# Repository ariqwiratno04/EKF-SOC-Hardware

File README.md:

# Extended kalman FIilter for SoC Estimation

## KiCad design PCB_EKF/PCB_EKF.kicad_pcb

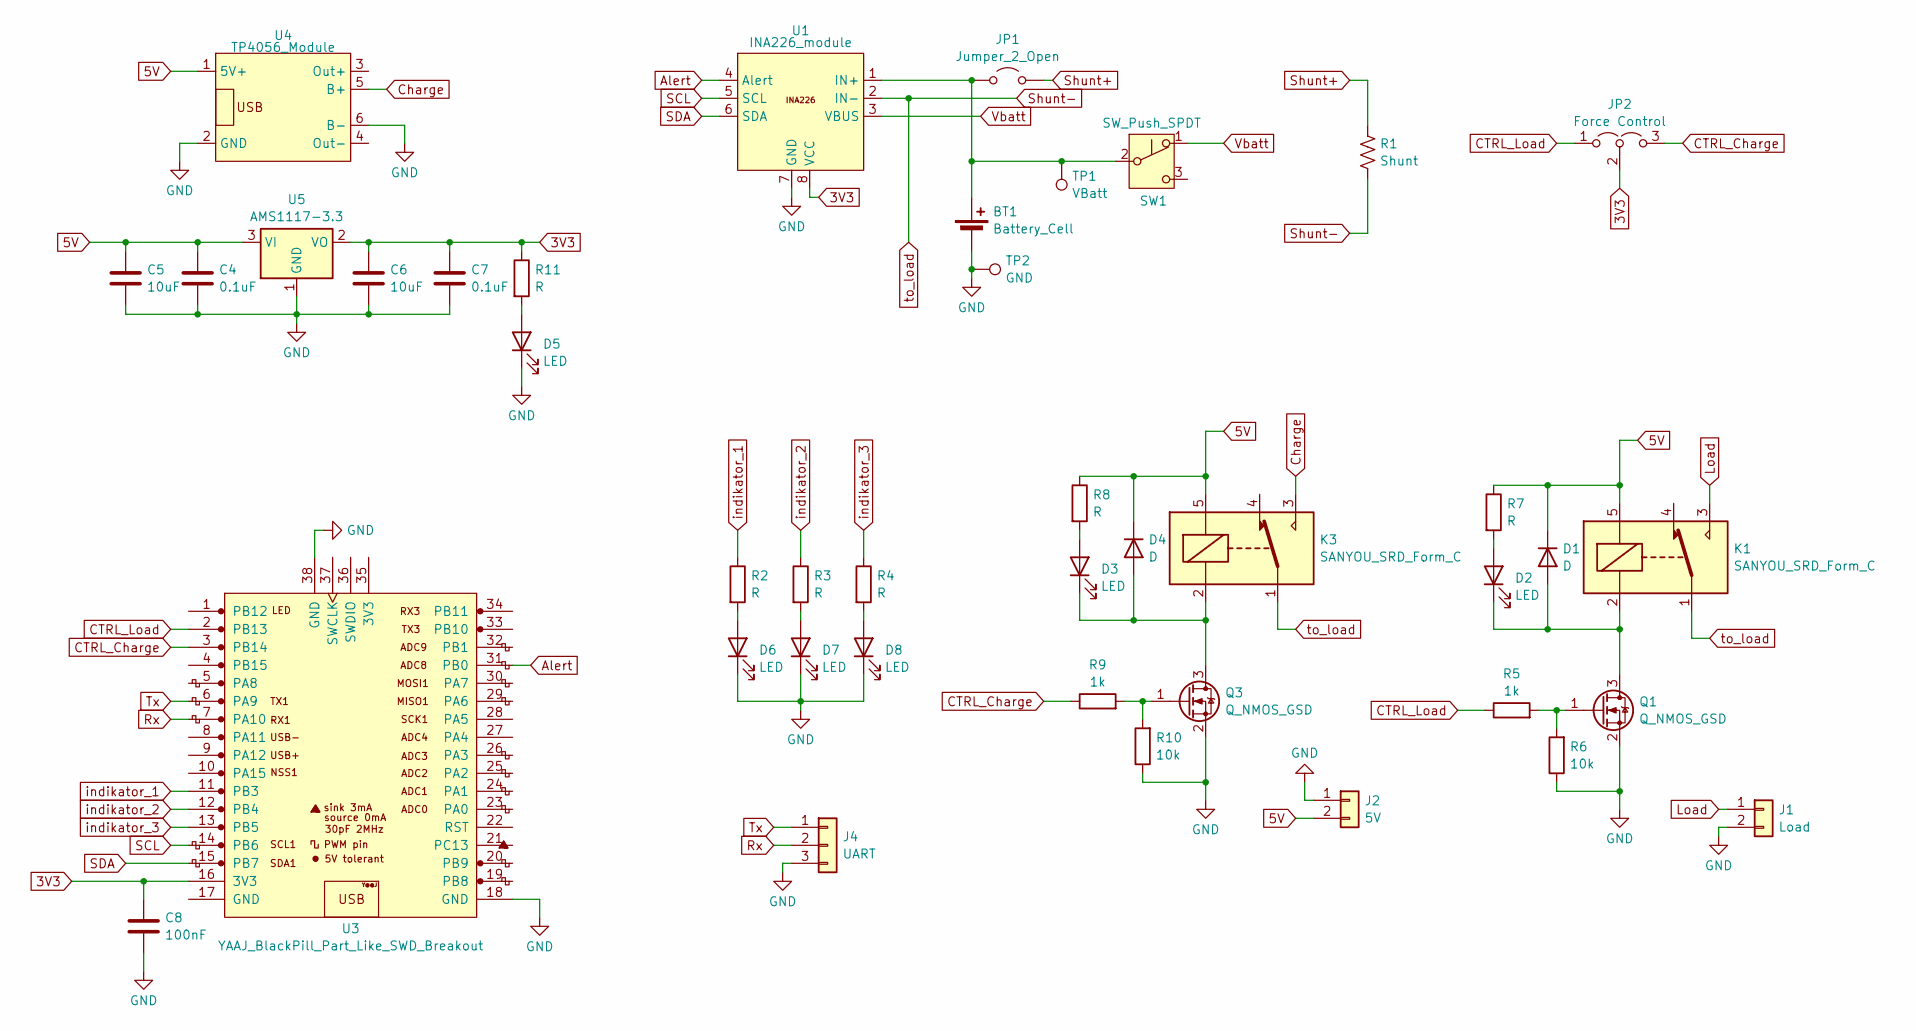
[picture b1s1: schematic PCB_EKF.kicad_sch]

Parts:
BT1: Battery_Cell; BatteryHolder_MPD_BH-18650-PC2
C4, C7: 0.1uF; C_0805_2012Metric
C5, C6: 10uF; C_0805_2012Metric
C8: 100nF; C_0805_2012Metric
D1, D4: D; D_SMA_Handsoldering
D2, D3, D5, D6, D7, D8: LED; LED_0805_2012Metric_Pad1.15x1.40mm_HandSolder
J1: Load; TerminalBlock_Phoenix_MKDS-1,5-2_1x02_P5.00mm_Horizontal
J2: 5V; TerminalBlock_Phoenix_MKDS-1,5-2_1x02_P5.00mm_Horizontal
J4: UART; PinHeader_1x03_P2.54mm_Vertical
JP1: Jumper_2_Open; SolderJumper-2_P1.3mm_Open_RoundedPad1.0x1.5mm
JP2: Force Control; PinHeader_1x03_P2.54mm_Vertical
K1, K3: SANYOU_SRD_Form_C; Relay_SPDT_SANYOU_SRD_Series_Form_C
Q1, Q3: Q_NMOS_GSD; SOT-23-3
R1: Shunt; R_2512_6332Metric_Pad1.40x3.35mm_HandSolder
R2, R3, R4, R7, R8, R11: R; R_0805_2012Metric
R5, R9: 1k; R_0805_2012Metric
R6, R10: 10k; R_0805_2012Metric
SW1: SW_Push_SPDT; SW_DIP_SPSTx01_Slide_9.78x4.72mm_W7.62mm_P2.54mm
TP1: VBatt; TestPoint_THTPad_1.5x1.5mm_Drill0.7mm
TP2: GND; TestPoint_THTPad_1.5x1.5mm_Drill0.7mm
U1: INA226_module
U3: YAAJ_BlackPill_Part_Like_SWD_Breakout; YAAJ_BlackPill_SWD_1
U4: TP4056_Module; TP4056-18650
U5: AMS1117-3.3; SOT-223-3_TabPin2

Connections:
3V3: C6.1, C7.1, C8.2, JP2.2 (C), R11.1, U1.8 (VCC), U3.16 (3V3), U5.2 (VO)
5V: C4.1, C5.1, D1.1 (K), D4.1 (K), J2.2, K1.5, K3.5, R7.1, R8.1, U4.1 (5V+), U5.3 (VI)
Alert: U1.4 (Alert), U3.31 (PB0)
CTRL_Charge: JP2.3 (B), R9.1, U3.3 (PB14)
CTRL_Load: JP2.1 (A), R5.1, U3.2 (PB13)
Charge: K3.3, U4.5 (B+)
GND: BT1.2 (-), C4.2, C5.2, C6.2, C7.2, C8.1, D5.1 (K), D6.1 (K), D7.1 (K), D8.1 (K), J1.2, J2.1, J4.3, Q1.2 (S), Q3.2 (S), R6.1, R10.1, TP2.1, U1.7 (GND), U3.18 (GND), U3.38 (GND), U4.2 (GND), U4.6 (B-), U5.1 (GND)
Load: J1.1, K1.3
unnamed: BT1.1 (+), JP1.1 (A), SW1.2 (B), TP1.1, U1.1 (IN+)
unnamed: D1.2 (A), D2.1 (K), K1.2, Q1.3 (D)
unnamed: D2.2 (A), R7.2
unnamed: D3.2 (A), R8.2
unnamed: D3.1 (K), D4.2 (A), K3.2, Q3.3 (D)
unnamed: D5.2 (A), R11.2
unnamed: D6.2 (A), R2.2
unnamed: D7.2 (A), R3.2
unnamed: D8.2 (A), R4.2
unnamed: Q1.1 (G), R5.2, R6.2
unnamed: Q3.1 (G), R9.2, R10.2
Rx: J4.2, U3.7 (PA10)
SCL: U1.5 (SCL), U3.14 (PB6)
SDA: U1.6 (SDA), U3.15 (PB7)
Shunt+: JP1.2 (B), R1.1
Shunt-: K1.1, K3.1, R1.2, U1.2 (IN-)
Tx: J4.1, U3.6 (PA9)
Vbatt: SW1.1 (A), U1.3 (VBUS)
indikator_1: R2.1, U3.11 (PB3)
indikator_2: R3.1, U3.12 (PB4)
indikator_3: R4.1, U3.13 (PB5)

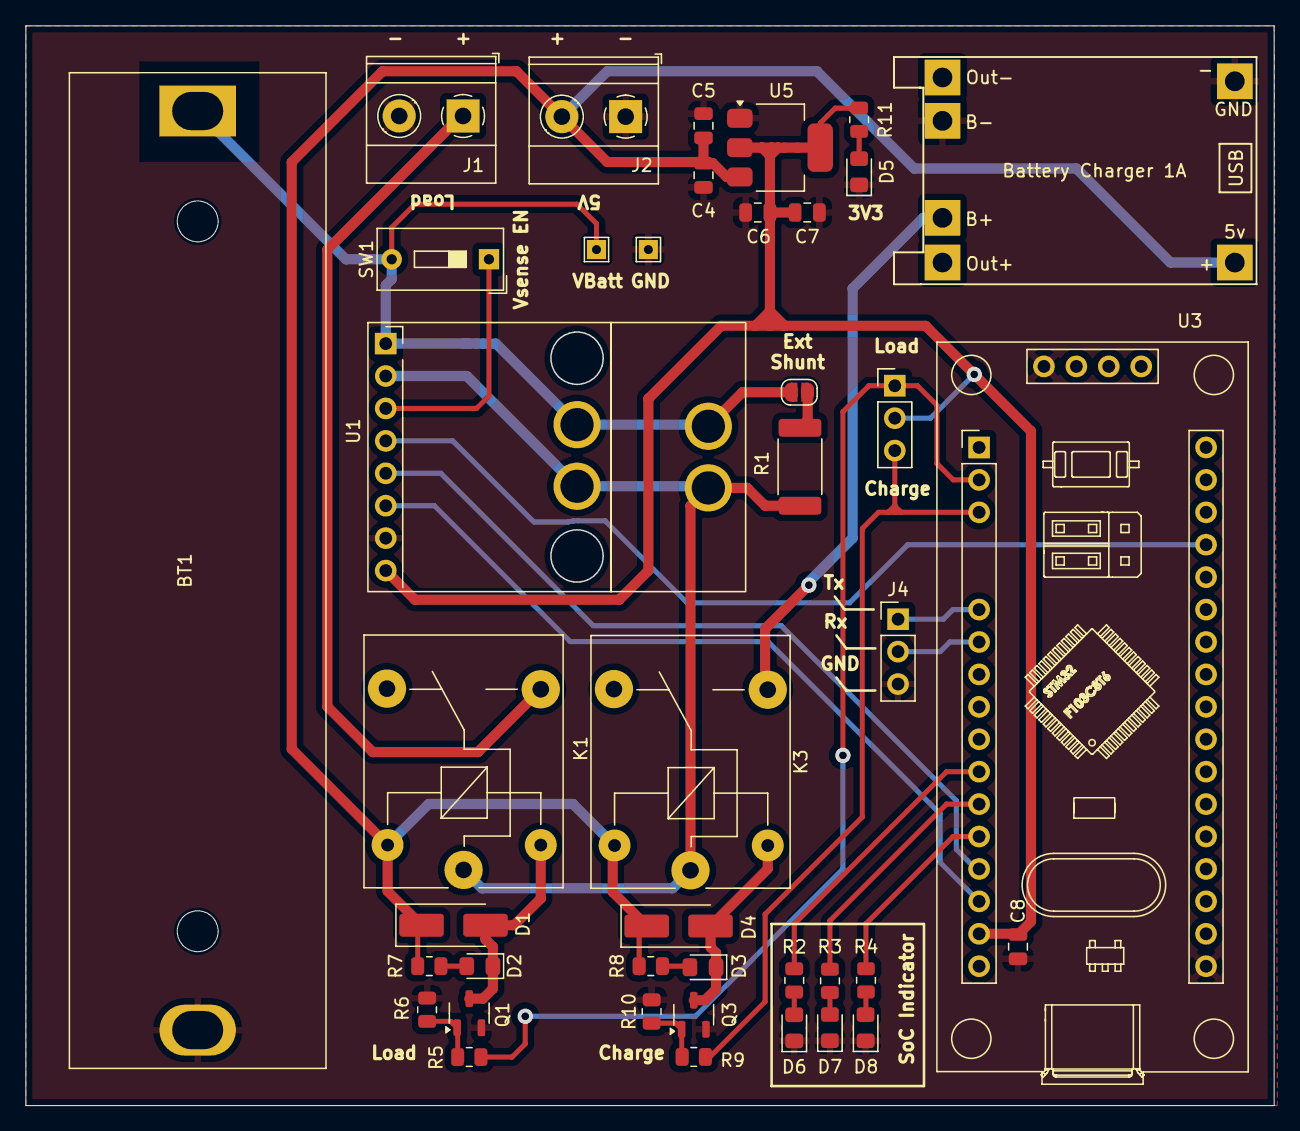
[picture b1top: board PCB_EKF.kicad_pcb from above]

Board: 2 copper layers, 97.7 x 84.5 mm, 41 parts (0 on the bottom side), 29 nets.

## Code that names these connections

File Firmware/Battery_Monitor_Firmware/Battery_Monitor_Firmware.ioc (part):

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Mcu.Name=STM32F411C(C-E)Ux
Mcu.Package=UFQFPN48
Mcu.UserName=STM32F411CEUx
PA10.Mode=Asynchronous
PA10.Signal=USART1_RX
PA11.Mode=Device_Only
PA11.Signal=USB_OTG_FS_DM
PA12.Mode=Device_Only
PA12.Signal=USB_OTG_FS_DP
PA13.Mode=Serial_Wire
PA13.Signal=SYS_JTMS-SWDIO
PA14.Mode=Serial_Wire
PA14.Signal=SYS_JTCK-SWCLK
PA9.Mode=Asynchronous
PA9.Signal=USART1_TX
PB0.GPIOParameters=GPIO_Label
PB0.GPIO_Label=Alert_INA226
PB0.Signal=GPIO_Input
PB13.GPIOParameters=GPIO_Label
PB13.GPIO_Label=CTRL_Charge
PB13.Signal=GPIO_Output
PB14.GPIOParameters=GPIO_Label
PB14.GPIO_Label=CTRL_Load
PB14.Signal=GPIO_Output
PB3.GPIOParameters=GPIO_Label
PB3.GPIO_Label=Indikator_1
PB3.Signal=GPIO_Output
PB4.GPIOParameters=GPIO_Label
PB4.GPIO_Label=Indikator_2
PB4.Signal=GPIO_Output
PB5.GPIOParameters=GPIO_Label
PB5.GPIO_Label=Indikator_3
PB5.Signal=GPIO_Output
PB6.Mode=I2C
PB6.Signal=I2C1_SCL
PB7.Mode=I2C
PB7.Signal=I2C1_SDA
PC13-ANTI_TAMP.GPIOParameters=GPIO_Label
PC13-ANTI_TAMP.GPIO_Label=LED_Built_in
PC13-ANTI_TAMP.Signal=GPIO_Output
PH0\ -\ OSC_IN.Mode=HSE-External-Oscillator
PH0\ -\ OSC_IN.Signal=RCC_OSC_IN
PH1\ -\ OSC_OUT.Mode=HSE-External-Oscillator
PH1\ -\ OSC_OUT.Signal=RCC_OSC_OUT
RCC.HSE_VALUE=25000000
RCC.SYSCLKFreq_VALUE=96000000
RCC.SYSCLKSource=RCC_SYSCLKSOURCE_PLLCLK
board=custom

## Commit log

2025-06-12 adding PCB files
2025-06-15 add firmware and change PCB
2025-06-15 minor change silkscreen
2025-07-14 add a lot
